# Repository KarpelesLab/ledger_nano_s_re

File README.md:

# Ledger Nano S — Hardware Reverse Engineering

Notes on the hardware of a Ledger Nano S, starting from photos of the bare
PCB. Raw photos are in [`pics/`](pics/). Zoomed crops of the key parts are in
[`docs/img/`](docs/img/).

**Interactive 3D board map: https://karpeleslab.github.io/ledger_nano_s_re/**

> **How sure are we?** Each item below is marked as one of:
> **[confirmed]** (read directly off the board), **[likely]** (strong
> evidence but not checked electrically) or **[hypothesis]** (needs probing).

## Photos

| File | Content |
|------|---------|
| `20261112_174544.JPG` | Back side, far half (button S1 / U4 end) |
| `20261112_174549.JPG` | Back side, USB half (5-pad header, U1 thermal vias) |
| `20261112_174600.JPG` | Front, USB half (J1, U1, U2, U3, S2) |
| `20261112_174607.JPG` | Front, far half (J2, U4, L1, S1) |
| `20261112_174622.JPG` | Front, far half (sharper) |
| `20261112_174629/34/41.JPG` | Front, USB half (several focus/lighting variants) |
| `20261112_183829/53.JPG` | Front, USB half, **components removed** (U1, U2, U3, J1, S2 off) |
| `20261112_183835/41.JPG` | Front, far half, **components removed** (J2, U4, L1, C1, C7-C9, S1 off) |
| `20261112_183926.JPG` | Removed U2 and U1, markings upright (ST pin-1 dot at bottom-left) |

The back-side photos are mirrored compared to the front: on the back the USB
connector is on the right.

## Board overview

- 2-layer-looking (maybe more) blue soldermask PCB, long thin strip that fits
  in the swivel case. Notches along the top edge line up with the case clips.
- All parts are on the front (top) side. The back has only traces, vias, test
  pads and the through-hole legs/tabs of J1 and the buttons.
- PCB date code on the back silkscreen: **`1751`** (likely 2017, week 51),
  next to the literal text `YWX` (probably the fab's year/week template
  label). This fits the component date codes (weeks 744 and 749 of 2017).
- An orange paint dot on the USB shield looks like a factory QC/inspection
  mark.
- The PCB edges are rough and fibrous all around. This could be from
  depanelization or from removing the board from its case.

## KiCad reconstruction

There is a KiCad 10 project in [`kicad/`](kicad/). It has the board outline,
every part placed from the photos, the photos as aligned underlay layers, and
a schematic with the nets known so far. Details and assumptions are in
[docs/kicad.md](docs/kicad.md).

**Interactive 3D view:** [online](https://karpeleslab.github.io/ledger_nano_s_re/kicad/viewer3d.html) or [`kicad/viewer3d.html`](kicad/viewer3d.html), published on GitHub Pages by
`.github/workflows/pages.yml` on every push to `master`. To open it locally, serve the `kicad/` folder
over HTTP (e.g. `python3 -m http.server -d kicad`). Hover a part for what it is and the net on
each pin, or a pad, track or via to light up its whole net on both sides. The board photos can be laid
on both faces. Rebuild its data (`kicad/scene.js`, `kicad/photo_*.jpg`) after editing the board with
`python3 tools/export_scene.py`.

## Bill of materials (as seen)

| Ref | Marking | Package | Identification |
|-----|---------|---------|----------------|
| **U1** | `F042K6` / `GQ22Z 1193` / `CHN 749 A`, ST logo, e3 | UFQFPN32 (5×5 mm) with exposed pad | **STM32F042K6** Cortex-M0, 32 KB Flash, 6 KB RAM, crystal-less USB FS. This is the main (non-secure) MCU. It handles USB, the display and the buttons. Date code 2017 wk 49. **[confirmed]** |
| **U2** | `NBO` / `PHL744` / `7B`, ST logo | DFN8 + exposed pad, **4.0 x 4.2 mm** (measured). Land pattern: pads 1.2 x 0.75 mm, pitch 0.98 mm, 2.1 x 3.45 mm EP with no vias | ST part, probably the **secure element** (ST31H320 family). ST prints internal codes rather than the part number. It is **not** an MFF2 package (MFF2 is 5x6 mm), so its pinout is ST's own (see below). Date 2017 wk 44. **[likely]** |
| **U3** | `AD30` | SOT-23-5 (3+2 leads), pin 1 dot next to "C12" | **3.0 V LDO**: pins 1 (VIN) and 3 (EN) on VBUS with input cap C12, pin 2 GND, pin 5 (VOUT) on the +3V0 rail (measured **2.997 V**). **[confirmed]** |
| **U4** | `8R00W` / `MYS749`, ST logo, e4 | DFN8 4×4 mm with exposed pad (2×3 thermal vias on the back) | **ST8R00**, a synchronous PWM step-up DC-DC converter. Input 4–6 V, so it must run from USB VBUS rather than the 3.0 V rail. Output is set to 6–12 V by a resistor divider. Switches at 1.7 MHz, up to 1 A. Its external parts are L1, C7–C9 and the R2/R4 divider. The 6–12 V output fits an SSD1306-class OLED panel VCC (7–15 V), so it **almost certainly powers the display**. Date 2017 wk 49. **[likely — marking + datasheet]** |
| **L1** | `100` | ~3×3 mm shielded power inductor | 10 µH. It is the inductor for the ST8R00 boost converter. **[likely]** |
| **J1** | — | Micro-USB B receptacle, SMD with through-hole shield tabs | USB power and data. **[confirmed]** |
| **J2** | pin 1 / pin 12 marked | 12-pin FPC/FFC connector, bottom-contact flip-lock | **OLED display** flex. The Nano S panel is a 128×32 monochrome OLED, usually driven by an SSD1306-class controller. **[likely]** |
| **S1, S2** | — | Side-actuated SMD tactile switches (kapton covered) | The two user buttons. **[confirmed]** |
| C2, C3, C5, C7, C8, C9, C10, C12 | — | 0402 / 0603 / 0805 MLCC | Decoupling and bulk caps. C7–C9 (0805) sit at the regulator. |
| C1 | — | 0603 | The cap just left of the "C7" label, next to the "C1" silkscreen (found while placing parts in KiCad). |
| R1, R2, R3, R4 | — | 0402 | R2/R4 are a pair next to U4. They are probably the ST8R00 feedback divider, which sets the output voltage (6–12 V). |

Crops: [U1](docs/img/u1_stm32f042k6.jpg) · [U2](docs/img/u2_marking.jpg) ·
[U3](docs/img/u3_ad30.jpg) · [U4](docs/img/u4_marking.jpg) ·
[J2](docs/img/j2_fpc.jpg) · [L1/C7–C9](docs/img/l1_c7-c9.jpg)

## U2 secure element pinout

U2 is a DFN8 measuring 4.0 × 4.2 mm, smaller than the MFF2 SIM package (5×6 mm).
The pinout is close to MFF2 but not identical (see below).

**Pin numbering:** the package dot is at the bottom-right in the front photos,
so going counter-clockwise from the top view:

```
            (towards U1/STM32)
              L1  ┌──────┐  R1
   pin 5 ───► ■   │      │   ■ ◄── pin 4
   pin 6 ───► ■   │  U2  │   ■ ◄── pin 3
   pin 7 ───► ■   │      │   ■ ◄── pin 2
   pin 8 ───► ■   │     •│   ■ ◄── pin 1
              L4  └──────┘  R4   (J2 side)
```

**What the board shows** (traces seen visually, not yet checked with a meter):

| Pin | Observation | Likely function |
|-----|-------------|-----------------|
| 1 | Not connected | NC |
| 2 | Connected to the ground pour | **GND** |
| 3 | STM32 **PA9** (USART1_TX), via the back | **I/O** (confirmed by ATR test) |
| 4 | Not connected | NC |
| 5 | STM32 **PA8** (USART1_CK / MCO) | **CLK** (confirmed by ATR test) |
| 6 | STM32 **PA10** (GPIO) | **RST** (confirmed by ATR test) |
| 7 | +3V0 rail (U3 out, U1.1), decoupled by C2 | **VCC** |
| 8 | Not connected | NC |

Crop: [u2_context.jpg](docs/img/u2_context.jpg)

**Relation to MFF2:** the pinout is MFF2-like, with the unused pair moved to
the other end of the package. Pins are listed as MFF2 (ETSI TS 102 671, from
memory) → U2:

| Pin | MFF2 | U2 |
|-----|------|----|
| 1 | C5 GND | NC |
| 2 | C6 SWP | GND |
| 3 | C7 I/O | I/O |
| 4 | C8 NC | NC |
| 5 | C4 NC | CLK |
| 6 | C3 CLK | RST |
| 7 | C2 RST | VCC |
| 8 | C1 VCC | NC |

Pins 5–8 are the MFF2 sequence (unused, CLK, RST, VCC) with the unused pin
moved to the end. Pins 1–4 have I/O and the unused SWP slot swapped compared
to a straight shift. That puts **pin 6 = RST**, so PA10 is the SE reset.

Pins 3, 5 and 6 go to PA9 (USART1_TX), PA8 (USART1_CK) and PA10 (GPIO). That
is the STM32 USART1 **smartcard-mode** wiring: TX as the half-duplex I/O line,
CK as the card clock, and a GPIO as RST. So the MCU ↔ SE link is ISO 7816-3
over USART1. See [docs/tracing.md](docs/tracing.md).

### ATR test (chip removed from the board)

The removed U2 was wired to a Baochip-1x (dabao): 3.3 V to pin 7, GND to pin
2, PB1 to pin 6 (RST), PB2 to pin 5 (CLK) and PB3 to pin 3 (I/O, 10 kΩ
pull-up to 3.3 V). Bit-banged ISO 7816-3 cold reset at a CLK of about 1.95 MHz,
using the `sc atr` command of the `iso7816-probe` branch of xous-core
(`baremetal/src/iso7816.rs`):

```
ATR: 3B 90 98 10 00      first start bit 823 clocks after RST, 0 parity errors
TS=3B direct convention
T0=90 TA1, TD1 present, no historical bytes
TA1=98 Fi=512, Di=12  ->  1 etu = 42.67 clocks
TD1=10 T=0, TA2 present
TA2=00 specific mode: T=0 at Fi/Di from TA1 (no PPS)
```

This confirms the pinout (3 = I/O, 5 = CLK, 6 = RST). The MCU ↔ SE link is
ISO 7816 **T=0**. Di index 8 is 12 in ISO's table, but Ledger uses it as 128:
the live capture below shows 4 clocks per bit, not 42.67.

### Live capture (MCU ↔ SE on a working device)

A logic analyzer capture of CLK, I/O and RST on a working Nano S is decoded in
[docs/seproxyhal_capture.md](docs/seproxyhal_capture.md); the protocol itself
(framing, every tag, and which ones each firmware version uses) is documented in
[docs/seproxyhal_protocol.md](docs/seproxyhal_protocol.md). In short:

- The MCU clocks the SE at **11.96 MHz**. The ATR comes at the default 372
  clocks per bit, then a PPS (`FF 10 98 77`) switches the link to **4 clocks
  per bit, about 3 Mbaud** (an earlier version of this README gave 45.6 kbaud
  from the ISO table).
- On top runs **SEPROXYHAL 1.6**: the SE draws the screen as BAGL elements,
  the MCU forwards buttons, ticks and USB events, and the SE answers USB
  enumeration itself. USB only comes up after the PIN is entered.
- At every boot the SE first **reads the MCU's whole 32 KB flash** over the
  link; the flash ends with a secp256k1 ECDSA signature over SHA-256 of the
  image. The captured **MCU 1.0 image is byte-for-byte Ledger's public
  `nanosr1` release**, signed under Ledger's documented root-of-trust key; MCU
  1.6 and 1.12 are signed with other (unknown) Ledger keys.
  `tools/mcu_flash_from_seph.py` rebuilds the image from a capture; the
  reconstructed images (needed for interoperability with the SE) are in
  [`mcu_firmware/`](mcu_firmware/).

## Back side / test access

- **5-pad row** with silkscreen rings near the top edge (USB half), with a
  dot marking one end. These are round solder-bumped pads, not plated
  through-holes. They form the STM32 **SWD port**: TP1 +3V0, TP2 SWCLK,
  TP3 GND, TP4 SWDIO, TP5 NRST. **[likely, traced]** Crop:
  [back_5pad_header.jpg](docs/img/back_5pad_header.jpg)
- 9 more **solder-bumped test pads** sit on the **OLED connector nets**:
  SPI SCK/MOSI, the PA0/PA1/PA2 control lines, and the J2.1/J2.10–12 power
  pins. They are bed-of-nails test points for the display interface.
  **[likely, traced]**
- **3×3 thermal via grid** = U1 exposed pad. **2×3 via grid** at the far end =
  U4 exposed pad.
- Large oval pads next to the USB end = J1 shield tabs.

## Architecture (traced; matches public Ledger documentation)

```
 USB ──J1── PA11/PA12 ─► STM32F042K6 (U1, "MCU")
                          │ USART1 smartcard: PA9=I/O, PA8=CLK 12 MHz, PA10=RST ─► ST31 SE (U2), 3 Mbaud
                          │ SPI1: PA5=SCK, PA7=MOSI + PA0/PA1/PA2 ─► J2 ─► 128×32 OLED
                          │ PA15 ◄─ S2      PB7 ◄─ S1
                          └ SWD: back header TP1..5 = 3V0, SWCLK, GND, SWDIO, NRST
 Power: VBUS (5 V) ─► U3 LDO (AD30) ─► +3V0 (MCU, SE, OLED VDD, U4 EN)
        VBUS (5 V) ─► L1 ─► U4 ST8R00 boost (R3/R4 FB) ─► J2.1 OLED panel VCC
```

In the Nano S design the MCU acts as a proxy. It owns USB, the screen and the
buttons. The secure element runs BOLOS and the apps, and it drives the UI
through the MCU (the "SEPROXYHAL" protocol).

## Next steps / TODO

The board is fully traced (both sides), every part and net is mapped, the U2
pinout and the MCU↔SE link are characterised, and the MCU firmware is captured
(see the sections above and [docs/](docs/)). What is still open:

- [ ] Probe the 5-pad header: continuity to U1 pins PA13 (SWDIO), PA14
      (SWCLK) and NRST. Try `st-link`/OpenOCD (it will probably be RDP-locked).
- [ ] Talk T=0 to the SE directly, at 4 clocks per bit after the PPS.
- [ ] Confirm the OLED supply: read R2/R4 (or measure the boost output), check
      it reaches J2, and whether the MCU drives the ST8R00 EN pin to switch the
      display power.
- [ ] Match the J2 pinout against the known SSD1306 FPC pinouts.

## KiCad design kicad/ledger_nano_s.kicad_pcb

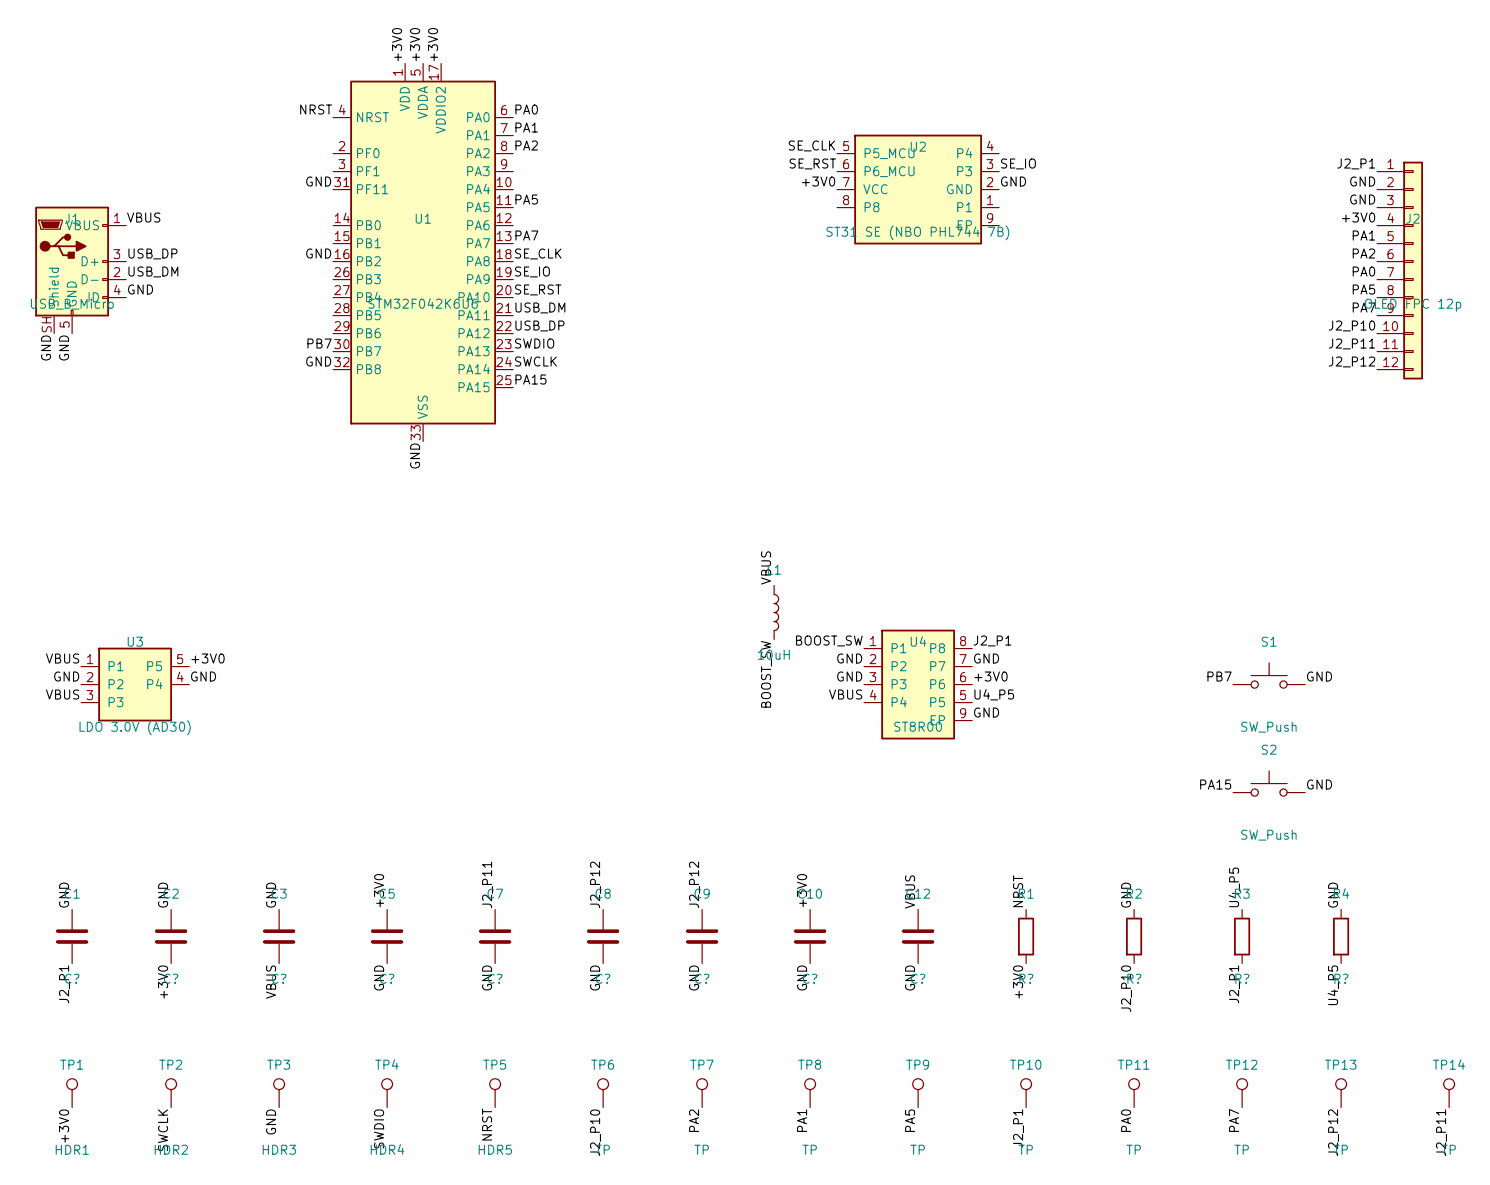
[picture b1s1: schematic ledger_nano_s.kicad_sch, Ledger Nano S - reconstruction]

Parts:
C1, C7, C8, C9: C?; C_0603_1608Metric
C2, C3, C5, C10, C12: C?; C_0402_1005Metric
J1: USB_B_Micro; USB_Micro-B_Molex-105017-0001
J2: OLED FPC 12p; FPC_12P_P0.5mm_Pin1Top
L1: 10uH; L_Abracon_ASPI-3012S
R1, R2, R3, R4: R?; R_0402_1005Metric
S1, S2: SW_Push; SW_SideTact_P3.8x1.38mm
TP1: HDR1; TestPoint_Pad_D1.5mm
TP2: HDR2; TestPoint_Pad_D1.5mm
TP3: HDR3; TestPoint_Pad_D1.5mm
TP4: HDR4; TestPoint_Pad_D1.5mm
TP5: HDR5; TestPoint_Pad_D1.5mm
TP6, TP7, TP8, TP9, TP10, TP11, TP12, TP13, TP14: TP; TestPoint_Pad_D1.0mm
U1: STM32F042K6U6; UFQFPN-32-1EP_5x5mm_P0.5mm_EP3.5x3.5mm
U2: ST31 SE (NBO PHL744 7B); ST_DFN8-1EP_4.0x4.2mm_P0.98mm
U3: LDO 3.0V (AD30); SOT-23-5
U4: ST8R00; DFN-8-1EP_4x4mm_P0.8mm_EP2.3x3.24mm

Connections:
+3V0: C2.2, C5.1, C10.1, J2.4, R1.2, TP1.1, U1.1 (VDD), U1.5 (VDDA), U1.17 (VDDIO2), U2.7 (VCC), U3.5, U4.6
BOOST_SW: L1.2, U4.1
GND: C1.1, C2.1, C3.1, C5.2, C7.2, C8.2, C9.2, C10.2, C12.2, J1.4 (ID), J1.5 (GND), J1.SH (Shield), J2.2, J2.3, J2.MP, R2.1, R4.1, S1.2, S2.2, TP3.1, U1.16 (PB2), U1.31 (PF11), U1.32 (PB8), U1.33 (VSS), U2.2 (GND), U3.2, U3.4, U4.2, U4.3, U4.7, U4.9 (EP)
J2_P1: C1.2, J2.1, R3.2, TP10.1, U4.8
J2_P10: J2.10, R2.2, TP6.1
J2_P11: C7.1, J2.11, TP14.1
J2_P12: C8.1, C9.1, J2.12, TP13.1
NRST: R1.1, TP5.1, U1.4 (NRST)
PA0: J2.7, TP11.1, U1.6 (PA0)
PA1: J2.5, TP8.1, U1.7 (PA1)
PA2: J2.6, TP7.1, U1.8 (PA2)
PA5: J2.8, TP9.1, U1.11 (PA5)
PA7: J2.9, TP12.1, U1.13 (PA7)
PA15: S2.1, U1.25 (PA15)
PB7: S1.1, U1.30 (PB7)
SE_CLK: U1.18 (PA8), U2.5 (P5_MCU)
SE_IO: U1.19 (PA9), U2.3
SE_RST: U1.20 (PA10), U2.6 (P6_MCU)
SWCLK: TP2.1, U1.24 (PA14)
SWDIO: TP4.1, U1.23 (PA13)
U4_P5: R3.1, R4.2, U4.5
USB_DM: J1.2 (D-), U1.21 (PA11)
USB_DP: J1.3 (D+), U1.22 (PA12)
VBUS: C3.2, C12.1, J1.1 (VBUS), L1.1, U3.1, U3.3, U4.4

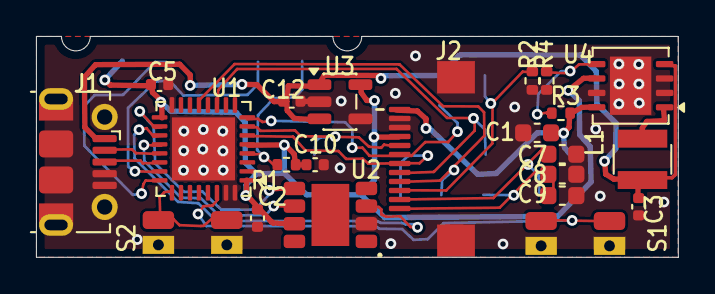
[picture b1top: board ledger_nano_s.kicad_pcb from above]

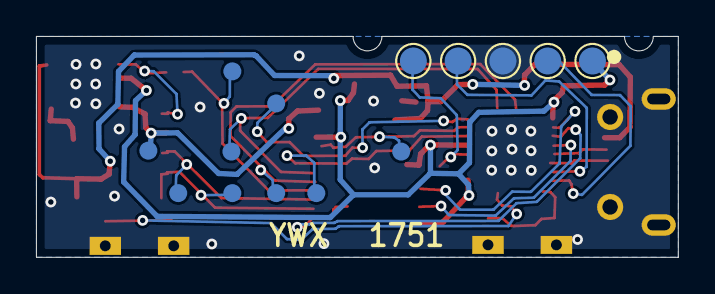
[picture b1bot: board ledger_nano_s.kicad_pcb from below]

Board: 2 copper layers, 35.7 x 12.3 mm, 36 parts (14 on the bottom side), 24 nets.

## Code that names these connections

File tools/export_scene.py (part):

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               notes="Inductor of the ST8R00 boost converter, from VBUS to its switch pin. Marked 100.",
               marking="100", mark_box=[1.6, 0.9, 0]),
    "J1": dict(title="Micro-USB B receptacle", package="SMD with through-hole shell tabs",
               notes="USB power and data. D- and D+ go straight to the MCU (PA11/PA12); the ID pin is "
                     "untraced (in the GND pour)."),
    "J2": dict(title="OLED display connector", package="12-pin FPC, 0.5 mm pitch, flip-lock",
               notes="Flex of the 128 x 32 monochrome OLED (SSD1306-class controller). Write-only 4-wire SPI "
                     "from SPI1 (PA5 clock, PA7 data) plus three control GPIOs (PA0, PA1, PA2), +3V0 logic "
                     "supply and the boost output for the panel."),
    "S1": dict(title="Right button", package="side-actuated tactile switch",
               notes="Reads on MCU PB7 (traced on the back along the bottom edge); the other side is GND."),
    "S2": dict(title="Left button", package="side-actuated tactile switch",
               notes="Reads on MCU PA15; the other side is GND."),
    "C1": dict(title="Capacitor", package="0603", notes="Boost converter output capacitor (OLED panel supply)."),
    "C2": dict(title="Capacitor", package="0402", notes="Decoupling of the secure element supply (+3V0 at U2 pin 7)."),
    "C3": dict(title="Capacitor", package="0402", notes="VBUS decoupling at the boost converter input."),
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    "R4": dict(title="Resistor", package="0402", notes="Bottom of the ST8R00 feedback divider, to ground."),
}
TESTPADS = {
    "TP1": "SWD header pin 1 (dot end): +3V0 supply", "TP2": "SWD header: SWCLK (MCU PA14)",
    "TP3": "SWD header: GND", "TP4": "SWD header: SWDIO (MCU PA13)", "TP5": "SWD header: NRST",
}

# Pin names that are not in a KiCad library symbol (or where it only has placeholders). "?" = inferred.
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    "VBUS": "USB 5 V: J1 pin 1 to the LDO input (U3) and the boost converter (L1, U4), via the back along the top edge.",
    "+3V0": "3.0 V rail from the LDO (U3 pin 5): MCU supplies, secure element VCC (U2 pin 7), OLED logic (J2 pin 4), "
            "ST8R00 pin 6 (probably its enable) and SWD header pin 1.",
    "USB_DM": "USB D-, J1 to MCU PA11.", "USB_DP": "USB D+, J1 to MCU PA12.",
    "SWDIO": "SWD data: MCU PA13 to SWD header TP4.", "SWCLK": "SWD clock: MCU PA14 to SWD header TP2.",
    "NRST": "MCU reset: SWD header TP5, with R1 pull-up.",
    "SE_CLK": "Secure element clock: MCU PA8 (USART1_CK, smartcard mode) to U2 pin 5, via the back.",
    "SE_RST": "Secure element reset: MCU PA10 (GPIO) to U2 pin 6, via the back.",
    "SE_IO": "Secure element I/O: MCU PA9 (USART1_TX, half-duplex smartcard) to U2 pin 3, along the bottom edge on "
             "the back. ISO 7816-3 T=0 at F/D 512/12; this line carries SEPROXYHAL.",
    "PA0": "OLED control GPIO (reset, chip select or data/command) to J2 pin 7; test pad TP11.",
    "PA1": "OLED control GPIO (reset or chip select) to J2 pin 5; test pad TP8.",
    "PA2": "OLED control GPIO (data/command or chip select) to J2 pin 6; test pad TP7.",
    "PA5": "OLED SPI clock (SPI1_SCK) to J2 pin 8; test pad TP9.",
    "PA7": "OLED SPI data (SPI1_MOSI) to J2 pin 9; test pad TP12.",
    "J2_P1": "Boost converter output (6-12 V, OLED panel VCC): U4 pin 8, R3, C1, J2 pin 1; test pad TP10.",
    "J2_P10": "J2 pin 10 with R2 to ground, likely the OLED controller's IREF; test pad TP6.",
    "J2_P11": "J2 pin 11 with C7 to ground, likely VCOMH; test pad TP14.",
    "J2_P12": "J2 pin 12 with C8 and C9 to ground; test pad TP13.",
    "BOOST_SW": "Boost converter switch node: L1 to U4 pin 1.",
    "U4_P5": "Boost converter feedback: the R3/R4 divider into U4 pin 5.",
    "PA15": "Left button S2 to MCU PA15.", "PB7": "Right button S1 to MCU PB7, along the bottom edge on the back.",
}


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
